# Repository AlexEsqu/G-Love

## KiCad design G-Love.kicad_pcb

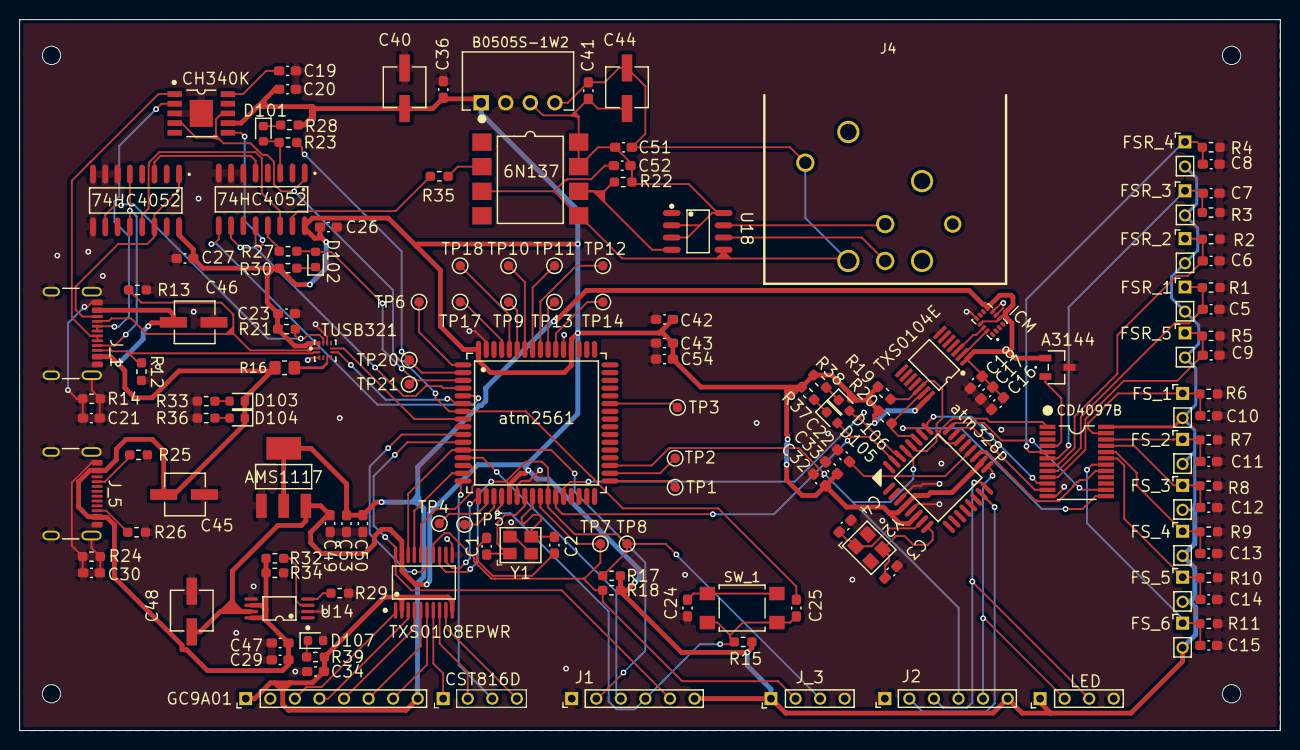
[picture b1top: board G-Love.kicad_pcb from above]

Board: 2 copper layers, 130.4 x 73.5 mm, 150 parts (0 on the bottom side), 111 nets.

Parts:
6N137: 6N137
74HC4052, 74HC4052#2: 74HC4052
A3144: Hall Sensor A3144; Hall_Sensor_A3144
AMS1117: AMS1117
B0505S-1W2: B0505S
C1, C2, C3, C4: 12pF; Capacitor_0603
C5, C6, C7, C8, C9, C10, C11, C12, C13, C14, C15: 47pF; Capacitor_0603
C16, C21: 10nF; Capacitor_0603
C17: 2.2nF; Capacitor_0603
C18: 0.1nF; Capacitor_0603
C19, C20, C22, C23, C24, C25, C26, C27, C32, C33, C34, C36, C41, C42, C43, C49, C50, C51, C52, C54: 100nF; Capacitor_0603
C29, C47: 1uF; Capacitor_0603
C30: 10n; Capacitor_0603
C40, C44, C45, C46, C48: 4.7uF; Capacitor_Electrolytic
C53: 10uF; Capacitor_0603
CD4097B: CD4097B
CH340K: CH340K
CST816D: CST816D; PinHeader_1x04_Pas2.54mm_cst816d
D101, D102, D105, D106: YELLOW; LED
D103, D104, D107: RED; LED
FSR_1, FSR_2, FSR_3, FSR_4, FSR_5: PinHeader_1x02_Pas2.54mm_
FS_1, FS_2, FS_3, FS_4, FS_5, FS_6: PinHeader_1x02_Pas2.54mm_
GC9A01: GC9A01_TFT; PinHeader_1x08_Pas2.54mm
ICM: ICM-42688-P_I2C; ICM-42688-P
J1, J2: PinHeader_1x06_Pas2.54mm
J4: XLR5_Ground; XLR5_Connector_Female_CONN-TH_NC5FAH
J_1, J_5: Conn_USB_Receptacle; USB_C_Receptacle_GCT_USB4105-xx-A_16P_TopMnt_Horizontal
J_3: PinHeader_1x04_Pas2.54mm
LED: PinHeader_1x06_Pas2.54mm; PinHeader_1x04_Pas2.54mm
R1, R2, R3, R4, R5, R6, R7, R8, R9, R10, R11, R15, R21, R34: 10kΩ; Resistor_0603
R12, R13, R25, R26: 5.1k; Resistor_0603
R14, R24: 1M; Resistor_0603
R16: 900K; Resistor_0805
R17, R18, R19, R20: 2.2kΩ; Resistor_0603
R22: 4.7k; Resistor_0603
R23, R27, R28, R30, R33, R36, R37, R38, R39: 1k; Resistor_0603
R29: 560R; Resistor_0603
R32: 47k; Resistor_0603
R35: 330R; Resistor_0603
SW_1: SW_SPST_TL3305A
TP1, TP2, TP3, TP4, TP5, TP6, TP7, TP8, TP9, TP10, TP11, TP12, TP13, TP14, TP17, TP18, TP20, TP21: TestPoint_Pad_D1.0mm
TUSB321: TUSB321
TXS0104E: TXS0104E; TXS0104EPWR
TXS0108EPWR: TXS0108EPWR; MTXS0108EPWR
U14: TPS2113APWR; TPS2113
U18: MAX485E; MAX485ED
Y1, Y2: 16MHz; Crystal_16MHz
atm328p: ATMega328P; ATMega328P-AU
atm2561: ATMEGA2561-16AU; ATMega2561

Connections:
+3.3V: A3144.1 (VCC), AMS1117.2 (Vout), C16.2, C17.1, C18.1, C34.1, C50.1, C53.1, GC9A01.1 (VCC), GC9A01.8 (BLK), ICM.5 (VDDIO), ICM.8 (VDD), ICM.12 (VDDIO), R39.1, TXS0104E.1 (V_{CCA}), TXS0108EPWR.2 (V_{CCA}), TXS0108EPWR.10 (OE)
/DTR: 74HC4052#2.1 (Y0), C25.2, CH340K.4 (~DTR), CH340K.8 (TXD), atm2561.7 (PE5_(OC3C/INT5))
/Data/power I/O/2561_UART_RX: R23.2, TP20.1, atm2561.2 (PE0_(RXD0/PCINT8/PDI))
/Data/power I/O/2561_UART_TX: D102.2 (K), R27.2, TP21.1, atm2561.3 (PE1_(TXD0/PDO))
/Data/power I/O/Data/DMX/TX_DMX: 74HC4052#2.15 (X2), R35.1
/Data/power I/O/Data/SBU1: 74HC4052.5 (Y1), 74HC4052.12 (X0), J_1.A8 (SBU1)
/Data/power I/O/Data/SBU2: 74HC4052.1 (Y0), 74HC4052.14 (X1), J_1.B8 (SBU2)
/Data/power I/O/Data/UD+: CH340K.1 (UD+), J_1.A7 (D+), J_1.B6 (D+)
/Data/power I/O/Data/UD-: CH340K.2 (UD-), J_1.A6 (D-), J_1.B7 (D-)
/Data/power I/O/Data/USB_SELECT: 74HC4052.10 (A), R21.2, TUSB321.11 (DIR)
/Data/power I/O/UART_MUX_SEL_A: 74HC4052#2.10 (A), atm2561.4 (PE2_(XCK0/AIN0))
/Data/power I/O/UART_MUX_SEL_B: 74HC4052#2.9 (B), atm2561.5 (PE3_(OC3A/AIN1))
/Data/power I/O/USB_INT1: TUSB321.7 (OUT1), atm2561.6 (PE4_(OC3B/INT4))
/Data/power I/O/USB_INT2: TUSB321.8 (OUT2), atm2561.8 (PE6_(T3/INT6))
/FingerTip Modules/FingerTip_I2C_SCL: J_3.2, R18.1, TP7.1, TXS0108EPWR.14 (B6), atm2561.25 ((SCL/INT0)_PD0)
/FingerTip Modules/FingerTip_I2C_SDA: J_3.3, R17.1, TP8.1, TXS0108EPWR.13 (B7), atm2561.26 ((SDA/INT1)_PD1)
/Hand_Captors/ADC_Mux_Inhibit: CD4097B.13 (INHIBIT), atm328p.26 (ADC3/PCINT11/PC3)
/Hand_Captors/ADC_Mux_Select_A: CD4097B.10 (A), atm328p.25 (ADC2/PCINT10/PC2)
/Hand_Captors/ADC_Mux_Select_B: CD4097B.11 (B), atm328p.23 (ADC0/PCINT8/PC0)
/Hand_Captors/ADC_Mux_Select_C: CD4097B.14 (C), atm328p.24 (ADC1/PCINT9/PC1)
/Hand_Captors/ADC_X_Output: CD4097B.1 (X_OutIn), atm328p.22 (ADC7)
/Hand_Captors/ADC_Y_Output: CD4097B.17 (Y_OutIn), atm328p.19 (ADC6)
/Hand_Captors/FSR_Index/TouchADC: C5.2, CD4097B.8 (X_1), FSR_1.1, R1.2
/Hand_Captors/FSR_Little/TouchADC: C8.2, CD4097B.5 (X_4), FSR_4.1, R4.2
/Hand_Captors/FSR_Middle/TouchADC: C6.2, CD4097B.7 (X_2), FSR_2.1, R2.2
/Hand_Captors/FSR_Ring/TouchADC: C7.2, CD4097B.6 (X_3), FSR_3.1, R3.2
/Hand_Captors/FSR_Thumb/TouchADC: C9.2, CD4097B.9 (X_0), FSR_5.1, R5.2
/Hand_Captors/Flex_Sensor0/FlexADC: C10.2, CD4097B.23 (Y_0), FS_1.1, R6.1
/Hand_Captors/Flex_Sensor1/FlexADC: C11.2, CD4097B.22 (Y_1), FS_2.1, R7.1
/Hand_Captors/Flex_Sensor2/FlexADC: C12.2, CD4097B.21 (Y_2), FS_3.1, R8.1
/Hand_Captors/Flex_Sensor3/FlexADC: C13.2, CD4097B.20 (Y_3), FS_4.1, R9.1
/Hand_Captors/Flex_Sensor4/FlexADC: C14.2, CD4097B.19 (Y_4), FS_5.1, R10.1
/Hand_Captors/Flex_Sensor5/FlexADC: C15.2, CD4097B.18 (Y_5), FS_6.1, R11.1
/Hand_Captors/HallCaptor/HallGPIO_Clasp: A3144.3 (Output), CD4097B.4 (X_5)
/Hand_Captors/I2C_IMU_SDA: R20.1, TXS0104E.13 (B1), atm328p.27 (SDA/ADC4/PSCINT12/PC4)
/Hand_Captors/I2C_IMU_SDK: R19.1, TXS0104E.12 (B2), atm328p.28 (SCL/ADC5/PCINT13/PC5)
/MCU_328_RESET: J2.4, atm328p.29 (~RESET/PCINT14/PC6), atm2561.35 (PC0_(A8))
/MCU_2561_RESET: C25.1, J1.4, R15.1, SW_1.2, atm2561.20 (~RESET)
/MISO_BOOT_328P: J2.2, atm328p.15 (OC2A/MOSI/PCINT3/PB3)
/MISO_BOOT_2561: J1.2, TXS0108EPWR.18 (B2), atm2561.12 ((MOSI/PCINT2)_PB2)
/MOSI_BOOT_328P: J2.3, LED.3, atm328p.16 (MISO/PCINT4/PB4)
/MOSI_BOOT_2561: J1.3, atm2561.13 ((MISO/PCINT3)_PB3)
/SCK_BOOT_328P: J2.5, LED.2, atm328p.17 (SCK/PCINT5/PB5)
/SCK_BOOT_2561: J1.5, TXS0108EPWR.20 (B1), atm2561.11 ((SCK/PCINT1)_PB1)
/Touchscreen/Screen_D/C: TXS0108EPWR.16 (B4), atm2561.14 ((OC2A/_PCINT4)_PB4)
/Touchscreen/Screen_RESET: TXS0108EPWR.17 (B3), atm2561.15 ((OC1A/PCINT5)_PB5)
/Touchscreen/Screen_SPI_SS: TXS0108EPWR.15 (B5), atm2561.10 ((~SS/PCINT0)_PB0)
/Touchscreen/Touch_I2C_INT: CST816D.5 (TP_INT), atm2561.16 ((OC1B/PCINT6)_PB6)
/Touchscreen/Touch_RESET: TXS0108EPWR.12 (B8), atm2561.17 ((OC0A/OC1C/PCINT7)_PB7)
GND: 74HC4052.6 (INH), 74HC4052.7 (VEE), 74HC4052.8 (GND), 74HC4052.9 (B), 74HC4052#2.6 (INH), 74HC4052#2.7 (VEE), 74HC4052#2.8 (GND), A3144.2 (GND), AMS1117.1 (GND), B0505S-1W2.2 (GND), C3.1, C4.1, C5.1, C6.1, C7.1, C8.1, C9.1, C10.1, C11.1, C12.1, C13.1, C14.1, C15.1, C16.1, C17.2, C18.2, C19.1, C20.1, C21.1, C21.2, C22.1, C23.1, C24.1, C26.2, C27.2, C29.1, C30.1, C30.2, C32.1, C33.2, C34.2, C36.2, C40.2, C42.1, C43.1, C45.2, C46.2, C47.1, C48.2, C49.2, C50.2, C53.2, C54.1, CD4097B.12 (VSS), CH340K.3 (GND), CH340K.11 (GND), D107.2 (K), GC9A01.2 (GND), ICM.6 (GND), ICM.7 (RESV), ICM.11 (RESV), J1.1, J2.1, J_1.A1 (GND), J_1.A12 (GND), J_1.B1 (GND), J_1.B12 (GND), J_1.SH (SHIELD), J_3.4, J_5.A1 (GND), J_5.A12 (GND), J_5.B1 (GND), J_5.B12 (GND), J_5.SH (SHIELD), LED.4, R1.1, R2.1, R3.1, R4.1, R5.1, R6.2, R7.2, R8.2, R9.2, R10.2, R11.2, R12.1, R13.1, R14.1, R14.2, R24.1, R24.2, R25.1, R26.1, R29.1, R33.1, R34.1, R36.1, TUSB321.3 (CURRENT_MODE), TUSB321.10 (GND), TXS0104E.7 (GND), TXS0108EPWR.11 (GND), U14.2 (~EN), U14.5 (GND), Y1.2 (G), Y1.4 (G), Y2.2 (G), Y2.4 (G), atm328p.3 (GND), atm328p.5 (GND), atm328p.21 (GND), atm2561.22 (GND_2), atm2561.53 (GND), atm2561.63 (GND_3)
unnamed: 6N137.3 (C), 6N137.5 (GND), B0505S-1W2.4 (0V), C41.2, C44.2, C51.1, C52.1, J4.1, J4.G, U18.5 (GND)
unnamed: 6N137.7 (EN), 6N137.8 (VCC), B0505S-1W2.3 (+VO), C41.1, C44.1, C51.2, C52.2, R22.2, U18.2 (~RE), U18.3 (DE), U18.8 (VCC)
unnamed: C1.2, C2.1
unnamed: C24.2, SW_1.1
unnamed: D101.1 (A), R28.2
unnamed: 74HC4052#2.3 (Y), D101.2 (K), R23.1
unnamed: D102.1 (A), R30.2
unnamed: D103.2 (K), R33.2
unnamed: D104.2 (K), R36.2
unnamed: D105.1 (A), R37.2
unnamed: D105.2 (K), atm328p.31 (TXD/PCINT17/PD1), atm2561.27 ((RXD1/INT2)_PD2)
unnamed: D106.1 (A), R38.2
unnamed: D106.2 (K), atm328p.30 (RDX/PCINT16/PD0), atm2561.28 ((TXD1/INT3)_PD3)
unnamed: D107.1 (A), R39.2
unnamed: J4.2, U18.7 (B)
unnamed: J_1.A5 (CC1), R13.2, TUSB321.1 (CC1)
unnamed: J_1.B5 (CC2), R12.2, TUSB321.2 (CC2)
unnamed: J_5.A5 (CC1), R25.2
unnamed: J_5.B5 (CC2), R26.2
unnamed: TP17.1, atm2561.61 (PF0_(ADC0))
unnamed: TP18.1, atm2561.60 (PF1_(ADC1))
unnamed: TP9.1, atm2561.59 (PF2_(ADC2))
unnamed: TP10.1, atm2561.58 (PF3_(ADC3))
unnamed: TP11.1, atm2561.57 (PF4_(ADC4/TCK))
unnamed: TP12.1, atm2561.56 (PF5_(ADC5/TMS))
unnamed: TP13.1, atm2561.55 (PF6_(ADC6/TDO))
unnamed: TP14.1, atm2561.54 (PF7_(ADC7/TDI))
unnamed: TP1.1, atm2561.33 (PG0_(~WR))
unnamed: TP2.1, atm2561.34 (PG1_(~RD))
unnamed: TP3.1, atm2561.43 (PG2_(ALE))
unnamed: TP4.1, atm2561.18 (PG3_(TOSC2))
unnamed: TP5.1, atm2561.19 (PG4_(TOSC1))
unnamed: TP6.1, atm2561.1 (PG5_(OC0B))
unnamed: C2.2, Y1.3, atm2561.24 (XTAL1)
unnamed: C1.1, Y1.1, atm2561.23 (XTAL2)
unnamed: C22.2, atm328p.20 (AREF)
unnamed: C4.2, Y2.1, atm328p.7 (XTAL1/TOSC1/PCINT6/PB6)
unnamed: C3.2, Y2.3, atm328p.8 (XTAL2/TOSC2/PCINT7/PB7)
unnamed: GC9A01.3 (SCL/SCK), TXS0108EPWR.1 (A1)
unnamed: GC9A01.4 (SDA/MOSI), TXS0108EPWR.3 (A2)
unnamed: GC9A01.5 (~RESET), TXS0108EPWR.4 (A3)
unnamed: GC9A01.6 (DC), TXS0108EPWR.5 (A4)
unnamed: GC9A01.7 (CS), TXS0108EPWR.6 (A5)
unnamed: CST816D.3 (TP_SCL), TXS0108EPWR.7 (A6)
unnamed: CST816D.4 (TP_SDA), TXS0108EPWR.8 (A7)
unnamed: CST816D.16 (TP_~RESET), TXS0108EPWR.9 (A8)
unnamed: ICM.13 (AP_SCK), TXS0104E.3 (A2)
unnamed: ICM.14 (AP_SDA), TXS0104E.2 (A1)
unnamed: R16.1, TUSB321.5 (VBUS_DET)
unnamed: 74HC4052#2.12 (X0), CH340K.6 (RXD)
unnamed: 74HC4052.13 (X), 74HC4052#2.14 (X1)
unnamed: 74HC4052#2.13 (X), R27.1
unnamed: 74HC4052.3 (Y), 74HC4052#2.5 (Y1)
unnamed: R29.2, U14.4 (ILIM)
unnamed: R32.2, U14.3 (VSNS)
unnamed: 6N137.2 (A), R35.2
unnamed: 6N137.6 (VO), R22.1, U18.4 (DI)
unnamed: J4.3, U18.6 (A)
unnamed: C19.2, CH340K.10 (V3)
VBUS: C29.2, C45.1, C46.1, C47.2, D103.1 (A), D104.1 (A), J_1.A4 (VBUS), J_1.A9 (VBUS), J_1.B4 (VBUS), J_1.B9 (VBUS), J_5.A4 (VBUS), J_5.A9 (VBUS), J_5.B4 (VBUS), J_5.B9 (VBUS), R16.2, R32.1, R34.2, U14.6 (IN2), U14.8 (IN1)
VCC: 74HC4052.16 (VCC), 74HC4052#2.16 (VCC), AMS1117.3 (Vin), B0505S-1W2.1 (VIN), C20.2, C23.2, C26.1, C27.1, C32.2, C33.1, C36.1, C40.1, C42.2, C43.2, C48.1, C49.1, C54.2, CD4097B.24 (VDD), CH340K.7 (VCC), FSR_1.2, FSR_2.2, FSR_3.2, FSR_4.2, FSR_5.2, FS_1.2, FS_2.2, FS_3.2, FS_4.2, FS_5.2, FS_6.2, J1.6, J2.6, J_3.1, LED.1, R15.2, R17.2, R18.2, R19.2, R20.2, R21.1, R28.1, R30.1, R37.1, R38.1, TUSB321.12 (VDD), TXS0104E.14 (V_{CCB}), TXS0108EPWR.19 (V_{CCB}), U14.7 (OUT), atm328p.4 (VCC), atm328p.6 (VCC), atm328p.18 (AVCC), atm2561.21 (VCC_2), atm2561.52 (VCC), atm2561.64 (AVCC)

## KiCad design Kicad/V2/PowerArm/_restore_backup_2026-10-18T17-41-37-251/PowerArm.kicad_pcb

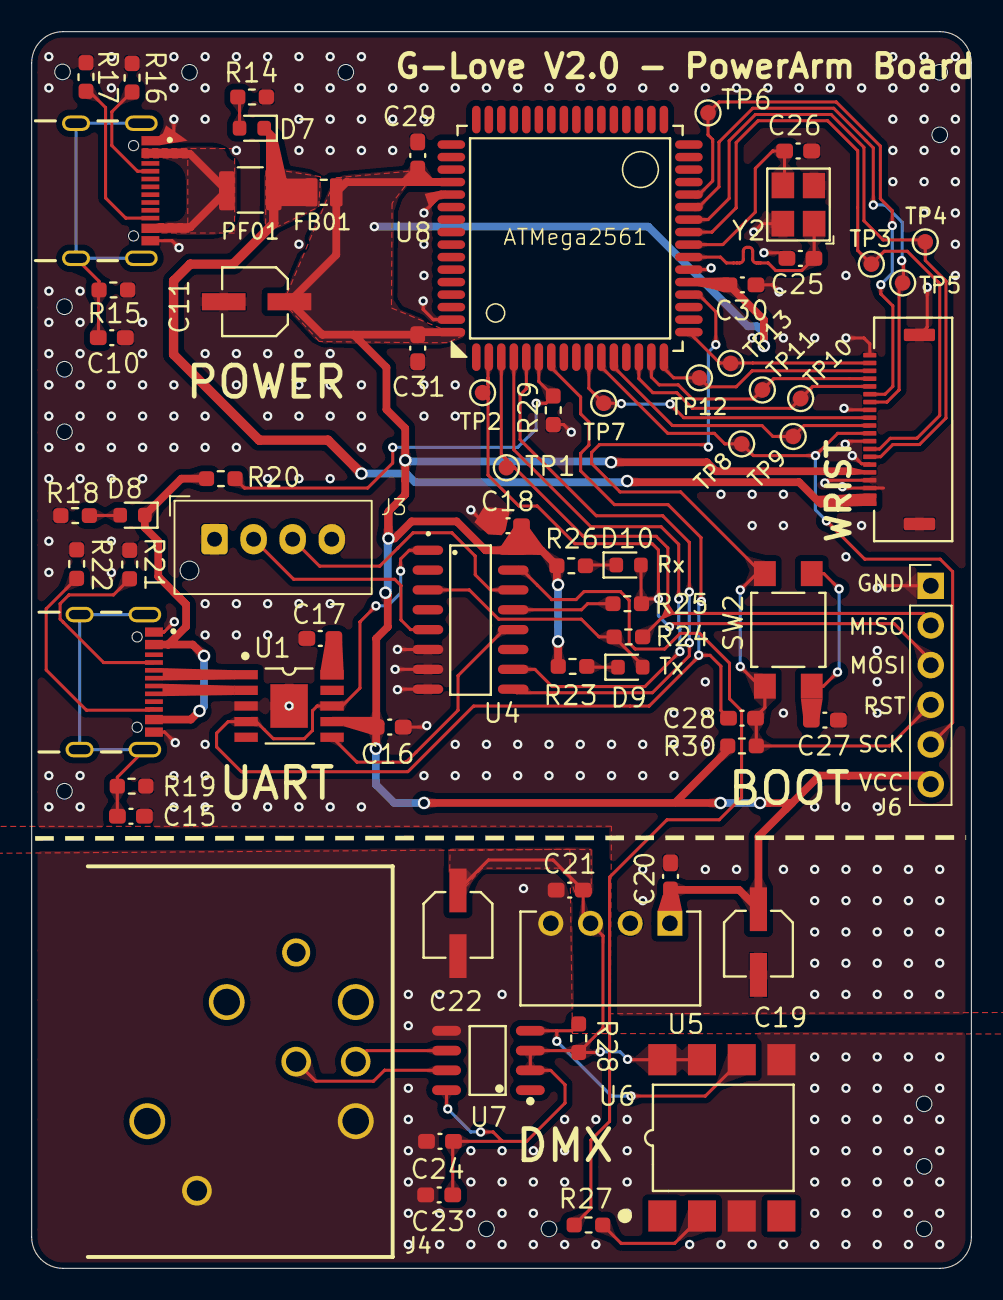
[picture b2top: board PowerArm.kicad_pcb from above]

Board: 2 copper layers, 60.1 x 79.1 mm, 69 parts (0 on the bottom side), 50 nets.

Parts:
C10: 10n; Capacitor_0603
C11, C19, C22: 4.7uF; Capacitor_Electrolytic
C15: 10nF; Capacitor_0603
C16, C17, C18, C20, C21, C23, C24, C27, C28, C29, C30, C31: 100nF; Capacitor_0603
C25, C26: 12pF; Capacitor_0603
D7: RED; LED
D8: GREEN; LED
D9, D10: YELLOW; LED
FB01: FERRITE BEAD
J1: JST_Connector_To_Wrist_Board; conn_zif_20x0.5mm
J2: USB Connector to Computer; USB_C_Receptacle_GCT_USB4105-xx-A_16P_TopMnt_Horizontal
J3: JST_Connector_To_Other_Glove; Conn_JST_4x2.50mm
J4: XLR5_Ground; XLR5_Connector_Female_CONN-TH_NC5FAH
J5: USB Connector to Powerbank; USB_C_Receptacle_GCT_USB4105-xx-A_16P_TopMnt_Horizontal
J6: PinHeader_1x06_P2.54mm_Vertical
PF01: POLYMER FUSE
R14, R18, R20, R23, R24, R25, R26: 1k; Resistor_0603
R15, R19: 1M; Resistor_0603
R16, R17: 5.1k; Resistor_0603
R21, R22: 5.1K; Resistor_0603
R27: 330R; Resistor_0603
R28: 4.7k; Resistor_0603
R29: 10k; Resistor_0603
R30: 10kΩ; Resistor_0603
SW2: SW_SPST_TL3305A
TP1, TP2, TP3, TP4, TP5, TP6, TP7, TP8, TP9, TP10, TP11, TP12, TP13: TestPoint_Pad_D1.0mm
U1: CH340K
U4: 74HC4052
U5: B0505S-1W1; B0505S
U6: 6N137
U7: MAX485E; MAX485ED
U8: ATMEGA2561-16AU; ATMega2561
Y2: 16MHz; Crystal_16MHz

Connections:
/ATMega2561/2561_MOSI: J1.11 (MOSI), TP9.1, U8.12 ((MOSI/PCINT2)_PB2)
/ATMega2561/2561_MUX_SELECT_A: U4.10 (A), U8.4 (PE2_(XCK0/AIN0))
/ATMega2561/2561_MUX_SELECT_B: U4.9 (B), U8.5 (PE3_(OC3A/AIN1))
/ATMega2561/2561_RXD1: J1.14 (2561_RX), TP5.1, U8.27 ((RXD1/INT2)_PD2)
/ATMega2561/2561_SCL: J1.8 (SCL), TP3.1, U8.25 ((SCL/INT0)_PD0)
/ATMega2561/2561_SCREEN_DC: J1.16 (SCREEN_DC), TP10.1, U8.14 ((OC2A/_PCINT4)_PB4)
/ATMega2561/2561_SCREEN_RESET: J1.17 (SCREEN_RESET), TP11.1, U8.15 ((OC1A/PCINT5)_PB5)
/ATMega2561/2561_SDA: J1.7 (SDA), TP4.1, U8.26 ((SDA/INT1)_PD1)
/ATMega2561/2561_SS: J1.12 (SS), TP7.1, U8.10 ((~SS/PCINT0)_PB0)
/ATMega2561/2561_TOUCH_INT: J1.18 (TOUCH_INT), TP12.1, U8.16 ((OC1B/PCINT6)_PB6)
/ATMega2561/2561_TOUCH_RESET: J1.19 (TOUCH_RESET), TP13.1, U8.17 ((OC0A/OC1C/PCINT7)_PB7)
/ATMega2561/2561_TXD1: J1.15 (2561_TX), TP6.1, U8.28 ((TXD1/INT3)_PD3)
/ATMega2561/2561_USB1_INT: R20.2, R29.2, U8.6 (PE4_(OC3B/INT4))
/ATMega2561/DTR: C28.2, U1.4 (~DTR), U1.8 (TXD), U4.1 (Y0), U8.7 (PE5_(OC3C/INT5))
/ATMega2561/MCU_2561_RESET: C28.1, J6.4, R30.1, SW2.2, U8.20 (~RESET)
/ATMega2561/MISO_BOOT_2561: J6.2, R24.2, TP1.1, U8.3 (PE1_(TXD0/PDO))
/ATMega2561/MOSI_BOOT_2561: D10.2 (K), J6.3, R25.2, TP2.1, U8.2 (PE0_(RXD0/PCINT8/PDI))
/ATMega2561/SCK_BOOT_2561: J1.10 (SCK), J6.5, TP8.1, U8.11 ((SCK/PCINT1)_PB1)
/Data/DMX/TX_DMX: R27.1, U4.15 (X2)
GND: C10.2, C11.2, C15.2, C16.1, C17.1, C18.2, C19.2, C20.2, C25.2, C26.1, C27.1, C29.2, C30.2, C31.2, J1.3 (GND), J1.4 (GND), J1.6 (GND), J1.9 (GND), J1.13 (GND), J1.20 (GND), J3.1 (GND), J3.4 (GND), J6.1, R14.1, R15.2, R16.1, R17.1, R18.1, R19.2, R21.2, R22.2, R29.1, U1.3 (GND), U1.11 (GND), U4.6 (INH), U4.7 (VEE), U4.8 (GND), U5.2 (GND), U8.22 (GND_2), U8.53 (GND), U8.63 (GND_3), Y2.2 (G), Y2.4 (G)
unnamed: C27.2, SW2.1
unnamed: D7.2 (K), R14.2
unnamed: D8.2 (K), R18.2
unnamed: D9.1 (A), R23.2
unnamed: D9.2 (K), R24.1, U4.3 (Y)
unnamed: D10.1 (A), R26.2
unnamed: J2.A5 (CC1), R21.1
unnamed: J2.B5 (CC2), R22.1
unnamed: C15.1, J2.SH (SHIELD), R19.1
unnamed: J3.3 (Rx), U4.14 (X1)
unnamed: J3.2 (Tx), U4.5 (Y1)
unnamed: C21.2, C22.2, C23.1, C24.1, J4.1, J4.G, U5.4 (0V), U6.3 (C), U6.5 (GND), U7.5 (GND)
unnamed: J4.2, U7.7 (B)
unnamed: J5.A5 (CC1), R16.2
unnamed: J5.B5 (CC2), R17.2
unnamed: C10.1, J5.SH (SHIELD), R15.1
unnamed: U1.6 (RXD), U4.12 (X0)
unnamed: J2.A6 (D-), J2.B7 (D-), U1.1 (UD+)
unnamed: J2.A7 (D+), J2.B6 (D+), U1.2 (UD-)
unnamed: C17.2, U1.10 (V3)
unnamed: R25.1, U4.13 (X)
unnamed: C21.1, C22.1, C23.2, C24.2, R28.2, U5.3 (+VO), U6.7 (EN), U6.8 (VCC), U7.2 (~RE), U7.3 (DE), U7.8 (VCC)
unnamed: R27.2, U6.2 (A)
unnamed: R28.1, U6.6 (VO), U7.4 (DI)
unnamed: J4.3, U7.6 (A)
unnamed: C26.2, U8.24 (XTAL1), Y2.3
unnamed: C25.1, U8.23 (XTAL2), Y2.1
VBUS: D8.1 (A), PF01.1, R20.1
VCC: C11.1, C16.2, C18.1, C19.1, C20.1, C29.1, C30.1, C31.1, FB01.2, J1.5 (5V), J6.6, R23.1, R26.1, R30.2, U1.7 (VCC), U4.16 (VCC), U5.1 (VIN), U8.21 (VCC_2), U8.52 (VCC), U8.64 (AVCC)
VCCL: D7.1 (A), FB01.1, J1.1 (5V_LED), J1.2 (5V_LED), PF01.2

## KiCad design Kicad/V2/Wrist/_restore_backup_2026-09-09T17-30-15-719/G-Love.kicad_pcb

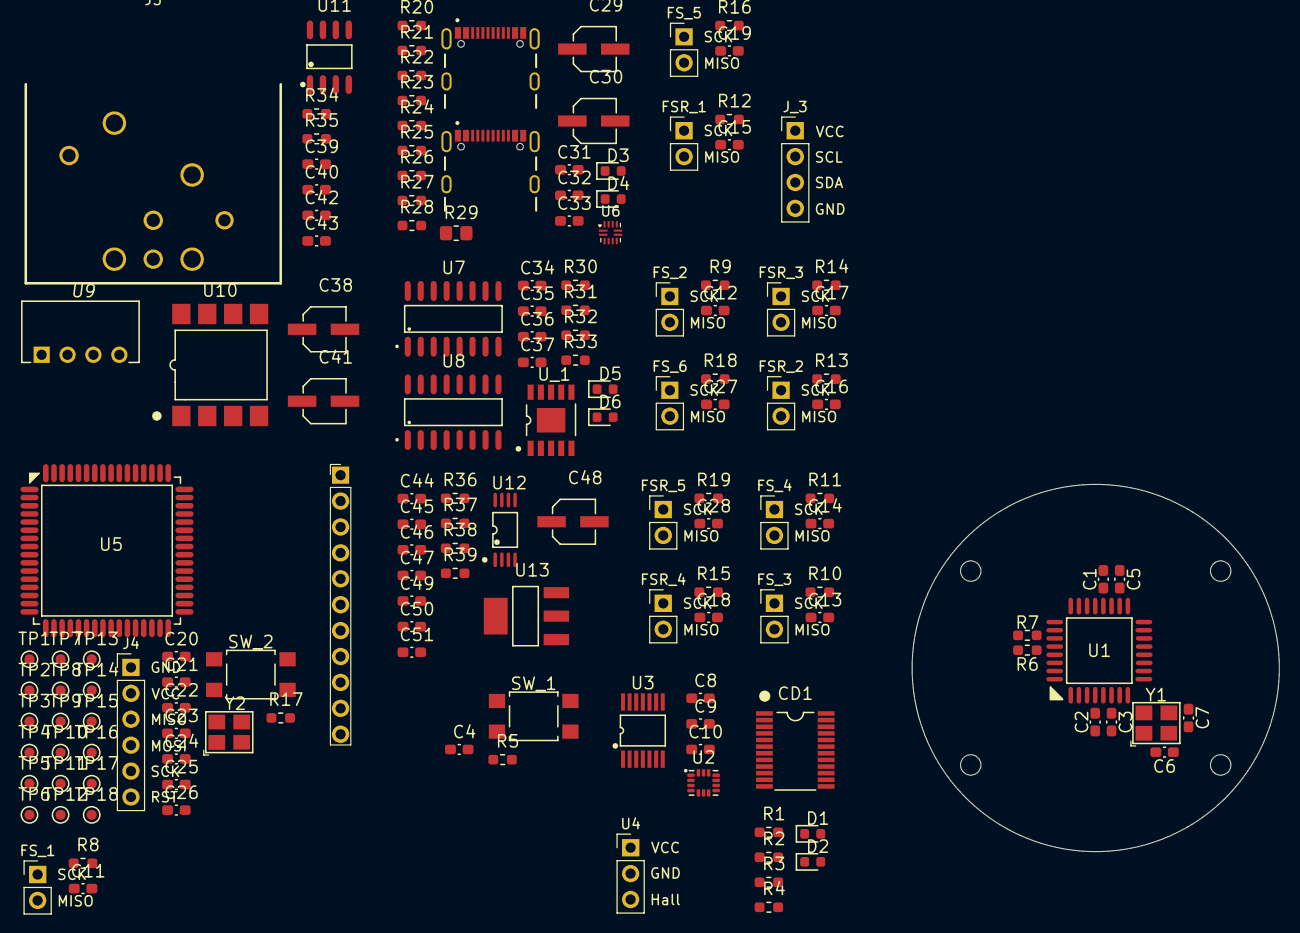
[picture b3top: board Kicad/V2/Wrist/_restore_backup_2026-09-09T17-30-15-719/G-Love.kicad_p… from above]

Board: 2 copper layers, 36.0 x 36.0 mm, 150 parts (0 on the bottom side), 101 nets, no tracks yet.

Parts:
C1, C2, C3, C4, C5, C22, C23, C24, C25, C26, C33, C34, C35, C36, C37, C39, C40, C42, C43, C47, C49, C51: 100nF; Capacitor_0603
C6, C7, C20, C21: 12pF; Capacitor_0603
C8, C31: 10nF; Capacitor_0603
C9: 2.2nF; Capacitor_0603
C10: 0.1nF; Capacitor_0603
C11, C12, C13, C14, C15, C16, C17, C18, C19, C27, C28: 47pF; Capacitor_0603
C29, C30, C38, C41, C48: 4.7uF; Capacitor_Electrolytic
C32: 10n; Capacitor_0603
C44, C45, C46: 1uF; Capacitor_0603
C50: 10uF; Capacitor_0603
CD1: CD4097B
D1, D2, D5, D6: YELLOW; LED
D3, D4: RED; LED
FSR_1, FSR_2, FSR_3, FSR_4, FSR_5: PinHeader_1x02_P2.54mm_Vertical
FS_1, FS_2, FS_3, FS_4, FS_5, FS_6: PinHeader_1x02_P2.54mm_Vertical
J3: PinHeader_1x11_P2.54mm_Vertical
J4: PinHeader_1x06_P2.54mm_Vertical
J5: XLR5_Ground; XLR5_Connector_Female_CONN-TH_NC5FAH
J_1, J_2: Conn_USB_Receptacle; USB_C_Receptacle_GCT_USB4105-xx-A_16P_TopMnt_Horizontal
J_3: PinHeader_1x04_P2.54mm_Vertical
R1, R2, R6, R7: 2.2kΩ; Resistor_0603
R3, R4: 1K; Resistor_0603
R5, R8, R9, R10, R11, R12, R13, R14, R15, R16, R17, R18, R19, R28, R37, R39: 10kΩ; Resistor_0603
R20, R21, R30, R31, R32, R33: 1k; Resistor_0603
R22, R23: 1M; Resistor_0603
R24, R25, R26, R27: 5.1k; Resistor_0603
R29: 900K; Resistor_0805
R34: 330R; Resistor_0603
R35: 4.7k; Resistor_0603
R36: 560R; Resistor_0603
R38: 47k; Resistor_0603
SW_1, SW_2: SW_SPST_TL3305A
TP1, TP2, TP3, TP4, TP5, TP6, TP7, TP8, TP9, TP10, TP11, TP12, TP13, TP14, TP15, TP16, TP17, TP18: TestPoint_Pad_D1.0mm
U1: ATMega328P; ATMega328P-AU
U2: ICM-42688-P_I2C; ICM-42688-P
U3: TXS0104E; TXS0104EPWR
U4: Hall Sensor A3144; PinHeader_1x03_P2.54mm_Vertical
U5: ATMEGA2561-16AU; ATMega2561
U6: TUSB321; Texas_X2QFN-12_1.6x1.6mm_P0.4mm
U7, U8: 74HC4052
U9: B0505S-1W1; B0505S
U10: 6N137
U11: MAX485E; MAX485ED
U12: TPS2113APWR; TPS2113
U13: AMS1117
U_1: CH340K
Y1, Y2: 16MHz; Crystal_16MHz

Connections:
5VL: C44.1, C47.1, R37.2
+3.3V: C8.2, C9.1, C10.1, C50.1, C51.1, U2.5 (VDDIO), U2.8 (VDD), U2.12 (VDDIO), U3.1 (V_{CCA}), U4.1 (VCC), U13.2 (Vout)
/ATMega2561/2561_MOSI: J3.10, U5.12 ((MOSI/PCINT2)_PB2)
/ATMega2561/2561_MUX_SELECT_A: U5.4 (PE2_(XCK0/AIN0)), U8.10 (A)
/ATMega2561/2561_MUX_SELECT_B: U5.5 (PE3_(OC3A/AIN1)), U8.9 (B)
/ATMega2561/2561_RXD1: D2.2 (K), U1.31 (TXD/PCINT17/PD1), U5.27 ((RXD1/INT2)_PD2)
/ATMega2561/2561_SCL: J3.5, J_3.2, R1.1, TP17.1, U5.25 ((SCL/INT0)_PD0)
/ATMega2561/2561_SCREEN_DC: J3.7, U5.14 ((OC2A/_PCINT4)_PB4)
/ATMega2561/2561_SCREEN_RESET: J3.8, U5.15 ((OC1A/PCINT5)_PB5)
/ATMega2561/2561_SDA: J3.4, J_3.3, R2.1, TP18.1, U5.26 ((SDA/INT1)_PD1)
/ATMega2561/2561_SS: J3.6, U5.10 ((~SS/PCINT0)_PB0)
/ATMega2561/2561_TOUCH_INT: J3.2, U5.16 ((OC1B/PCINT6)_PB6)
/ATMega2561/2561_TOUCH_RESET: J3.3, U5.17 ((OC0A/OC1C/PCINT7)_PB7)
/ATMega2561/2561_TXD1: D1.2 (K), U1.30 (RDX/PCINT16/PD0), U5.28 ((TXD1/INT3)_PD3)
/ATMega2561/2561_USB1_INT: U5.6 (PE4_(OC3B/INT4)), U6.7 (OUT1)
/ATMega2561/2561_USB2_INT: U5.8 (PE6_(T3/INT6)), U6.8 (OUT2)
/ATMega2561/DTR: C23.2, U5.7 (PE5_(OC3C/INT5)), U8.1 (Y0), U_1.4 (~DTR), U_1.8 (TXD)
/ATMega2561/MCU_2561_RESET: C23.1, J4.4, R17.1, SW_2.2, U5.20 (~RESET)
/ATMega2561/MISO_BOOT_2561: J4.2, R31.2, TP1.1, U5.3 (PE1_(TXD0/PDO))
/ATMega2561/MOSI_BOOT_2561: D6.2 (K), J4.3, R32.2, TP2.1, U5.2 (PE0_(RXD0/PCINT8/PDI))
/ATMega2561/SCK_BOOT_2561: J3.9, J4.5, U5.11 ((SCK/PCINT1)_PB1)
/ATmega328p/328P_ADC_MUX_INH: CD1.13 (INHIBIT), U1.26 (ADC3/PCINT11/PC3)
/ATmega328p/328P_ADC_MUX_SELECT_A: CD1.10 (A), U1.25 (ADC2/PCINT10/PC2)
/ATmega328p/328P_ADC_MUX_SELECT_B: CD1.11 (B), U1.23 (ADC0/PCINT8/PC0)
/ATmega328p/328P_ADC_MUX_SELECT_C: CD1.14 (C), U1.24 (ADC1/PCINT9/PC1)
/ATmega328p/328P_ADC_X_OUT: CD1.1 (X_OutIn), U1.22 (ADC7)
/ATmega328p/328P_ADC_Y_OUT: CD1.17 (Y_OutIn), U1.19 (ADC6)
/ATmega328p/328P_I2C_IMU_SCL: R6.1, U1.28 (SCL/ADC5/PCINT13/PC5), U3.12 (B2)
/ATmega328p/328P_I2C_IMU_SDA: R7.1, U1.27 (SDA/ADC4/PSCINT12/PC4), U3.13 (B1)
/ATmega328p/MCU_328P_RESET: R5.1, SW_1.2, U1.29 (~RESET/PCINT14/PC6)
/Data/power I/O/Data/DMX/TX_DMX: R34.1, U8.15 (X2)
/Data/power I/O/Data/SBU1: J_1.A8 (SBU1), U7.5 (Y1), U7.12 (X0)
/Data/power I/O/Data/SBU2: J_1.B8 (SBU2), U7.1 (Y0), U7.14 (X1)
/Data/power I/O/Data/UD+: J_1.A7 (D+), J_1.B6 (D+), U_1.1 (UD+)
/Data/power I/O/Data/UD-: J_1.A6 (D-), J_1.B7 (D-), U_1.2 (UD-)
/Data/power I/O/Data/USB_SELECT: R28.2, U6.11 (DIR), U7.10 (A)
/Hand_Captors/FSR_Index/TouchADC: C15.2, CD1.8 (X_1), FSR_1.1, R12.2
/Hand_Captors/FSR_Little/TouchADC: C16.2, CD1.5 (X_4), FSR_2.1, R13.2
/Hand_Captors/FSR_Middle/TouchADC: C28.2, CD1.7 (X_2), FSR_5.1, R19.2
/Hand_Captors/FSR_Ring/TouchADC: C17.2, CD1.6 (X_3), FSR_3.1, R14.2
/Hand_Captors/FSR_Thumb/TouchADC: C18.2, CD1.9 (X_0), FSR_4.1, R15.2
/Hand_Captors/Flex_Sensor0/FlexADC: C14.2, CD1.23 (Y_0), FS_4.1, R11.1
/Hand_Captors/Flex_Sensor1/FlexADC: C27.2, CD1.22 (Y_1), FS_6.1, R18.1
/Hand_Captors/Flex_Sensor2/FlexADC: C13.2, CD1.21 (Y_2), FS_3.1, R10.1
/Hand_Captors/Flex_Sensor3/FlexADC: C12.2, CD1.20 (Y_3), FS_2.1, R9.1
/Hand_Captors/Flex_Sensor4/FlexADC: C11.2, CD1.19 (Y_4), FS_1.1, R8.1
/Hand_Captors/Flex_Sensor5/FlexADC: C19.2, CD1.18 (Y_5), FS_5.1, R16.1
/Hand_Captors/HallCaptor/HallGPIO_Clasp: CD1.4 (X_5), U4.3 (Output)
GND: C1.1, C2.1, C3.1, C4.1, C5.2, C6.1, C7.1, C8.1, C9.2, C10.2, C11.1, C12.1, C13.1, C14.1, C15.1, C16.1, C17.1, C18.1, C19.1, C20.2, C21.1, C22.1, C24.2, C25.2, C26.2, C27.1, C28.1, C29.2, C30.2, C31.2, C32.2, C33.1, C34.1, C35.1, C36.2, C37.2, C38.2, C39.2, C44.2, C45.1, C46.1, C47.2, C48.2, C49.2, C50.2, C51.2, CD1.12 (VSS), J3.1, J4.1, J_3.4, R8.2, R9.2, R10.2, R11.2, R12.1, R13.1, R14.1, R15.1, R16.2, R18.2, R19.1, R20.1, R21.1, R22.2, R23.2, R24.1, R25.1, R26.1, R27.1, R36.1, R37.1, R39.1, U1.3 (GND), U1.5 (GND), U1.21 (GND), U2.6 (GND), U2.7 (RESV), U2.11 (RESV), U3.7 (GND), U4.2 (GND), U5.22 (GND_2), U5.53 (GND), U5.63 (GND_3), U6.3 (CURRENT_MODE), U6.10 (GND), U7.6 (INH), U7.7 (VEE), U7.8 (GND), U7.9 (B), U8.6 (INH), U8.7 (VEE), U8.8 (GND), U9.2 (GND), U12.2 (~EN), U12.5 (GND), U13.1 (GND), U_1.3 (GND), U_1.11 (GND), Y1.2 (G), Y1.4 (G), Y2.2 (G), Y2.4 (G)
unnamed: C4.2, SW_1.1
unnamed: C22.2, SW_2.1
unnamed: D1.1 (A), R3.1
unnamed: D2.1 (A), R4.1
unnamed: D3.2 (K), R20.2
unnamed: D4.2 (K), R21.2
unnamed: D5.1 (A), R30.2
unnamed: D5.2 (K), R31.1, U8.3 (Y)
unnamed: D6.1 (A), R33.2
unnamed: C40.2, C41.2, C42.1, C43.1, J5.1, J5.G, U9.4 (0V), U10.3 (C), U10.5 (GND), U11.5 (GND)
unnamed: J5.2, U11.7 (B)
unnamed: J_1.A5 (CC1), R26.2, U6.1 (CC1)
unnamed: J_1.B5 (CC2), R27.2, U6.2 (CC2)
unnamed: C31.1, J_1.SH (SHIELD), R22.1
unnamed: J_2.A5 (CC1), R24.2
unnamed: J_2.B5 (CC2), R25.2
unnamed: C32.1, J_2.SH (SHIELD), R23.1
unnamed: C1.2, U1.20 (AREF)
unnamed: C6.2, U1.7 (XTAL1/TOSC1/PCINT6/PB6), Y1.1
unnamed: C7.2, U1.8 (XTAL2/TOSC2/PCINT7/PB7), Y1.3
unnamed: U2.13 (AP_SCK), U3.3 (A2)
unnamed: U2.14 (AP_SDA), U3.2 (A1)
unnamed: TP9.1, U5.61 (PF0_(ADC0))
unnamed: TP10.1, U5.60 (PF1_(ADC1))
unnamed: TP11.1, U5.59 (PF2_(ADC2))
unnamed: TP12.1, U5.58 (PF3_(ADC3))
unnamed: TP13.1, U5.57 (PF4_(ADC4/TCK))
unnamed: TP14.1, U5.56 (PF5_(ADC5/TMS))
unnamed: TP15.1, U5.55 (PF6_(ADC6/TDO))
unnamed: TP16.1, U5.54 (PF7_(ADC7/TDI))
unnamed: TP3.1, U5.33 (PG0_(~WR))
unnamed: TP4.1, U5.34 (PG1_(~RD))
unnamed: TP5.1, U5.43 (PG2_(ALE))
unnamed: TP6.1, U5.18 (PG3_(TOSC2))
unnamed: TP7.1, U5.19 (PG4_(TOSC1))
unnamed: TP8.1, U5.1 (PG5_(OC0B))
unnamed: C21.2, U5.24 (XTAL1), Y2.3
unnamed: C20.1, U5.23 (XTAL2), Y2.1
unnamed: R29.1, U6.5 (VBUS_DET)
unnamed: U7.13 (X), U8.14 (X1)
unnamed: U7.3 (Y), U8.5 (Y1)
unnamed: U8.12 (X0), U_1.6 (RXD)
unnamed: R32.1, U8.13 (X)
unnamed: R34.2, U10.2 (A)
unnamed: C40.1, C41.1, C42.2, C43.2, R35.2, U9.3 (+VO), U10.7 (EN), U10.8 (VCC), U11.2 (~RE), U11.3 (DE), U11.8 (VCC)
unnamed: R35.1, U10.6 (VO), U11.4 (DI)
unnamed: J5.3, U11.6 (A)
unnamed: R36.2, U12.4 (ILIM)
unnamed: R38.2, U12.3 (VSNS)
unnamed: C35.2, U_1.10 (V3)
VBUS: C29.1, C30.1, C45.2, C46.2, D3.1 (A), D4.1 (A), R29.2, R38.1, R39.2, U12.6 (IN2), U12.8 (IN1)
VCC: C2.2, C3.2, C5.1, C24.1, C25.1, C26.1, C33.2, C34.2, C36.1, C37.1, C38.1, C39.1, C48.1, C49.1, CD1.24 (VDD), FSR_1.2, FSR_2.2, FSR_3.2, FSR_4.2, FSR_5.2, FS_1.2, FS_2.2, FS_3.2, FS_4.2, FS_5.2, FS_6.2, J3.11, J4.6, J_3.1, R1.2, R2.2, R3.2, R4.2, R5.2, R6.2, R7.2, R17.2, R28.1, R30.1, R33.1, U1.4 (VCC), U1.6 (VCC), U1.18 (AVCC), U3.14 (V_{CCB}), U5.21 (VCC_2), U5.52 (VCC), U5.64 (AVCC), U6.12 (VDD), U7.16 (VCC), U8.16 (VCC), U9.1 (VIN), U12.7 (OUT), U13.3 (Vin), U_1.7 (VCC)
